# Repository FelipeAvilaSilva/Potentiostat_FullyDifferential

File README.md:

# Potentiostat_FullyDifferential
 Desenvolvimento de um Potenciostato Diferencial para detecção de metais pesados em corpos aquáticos

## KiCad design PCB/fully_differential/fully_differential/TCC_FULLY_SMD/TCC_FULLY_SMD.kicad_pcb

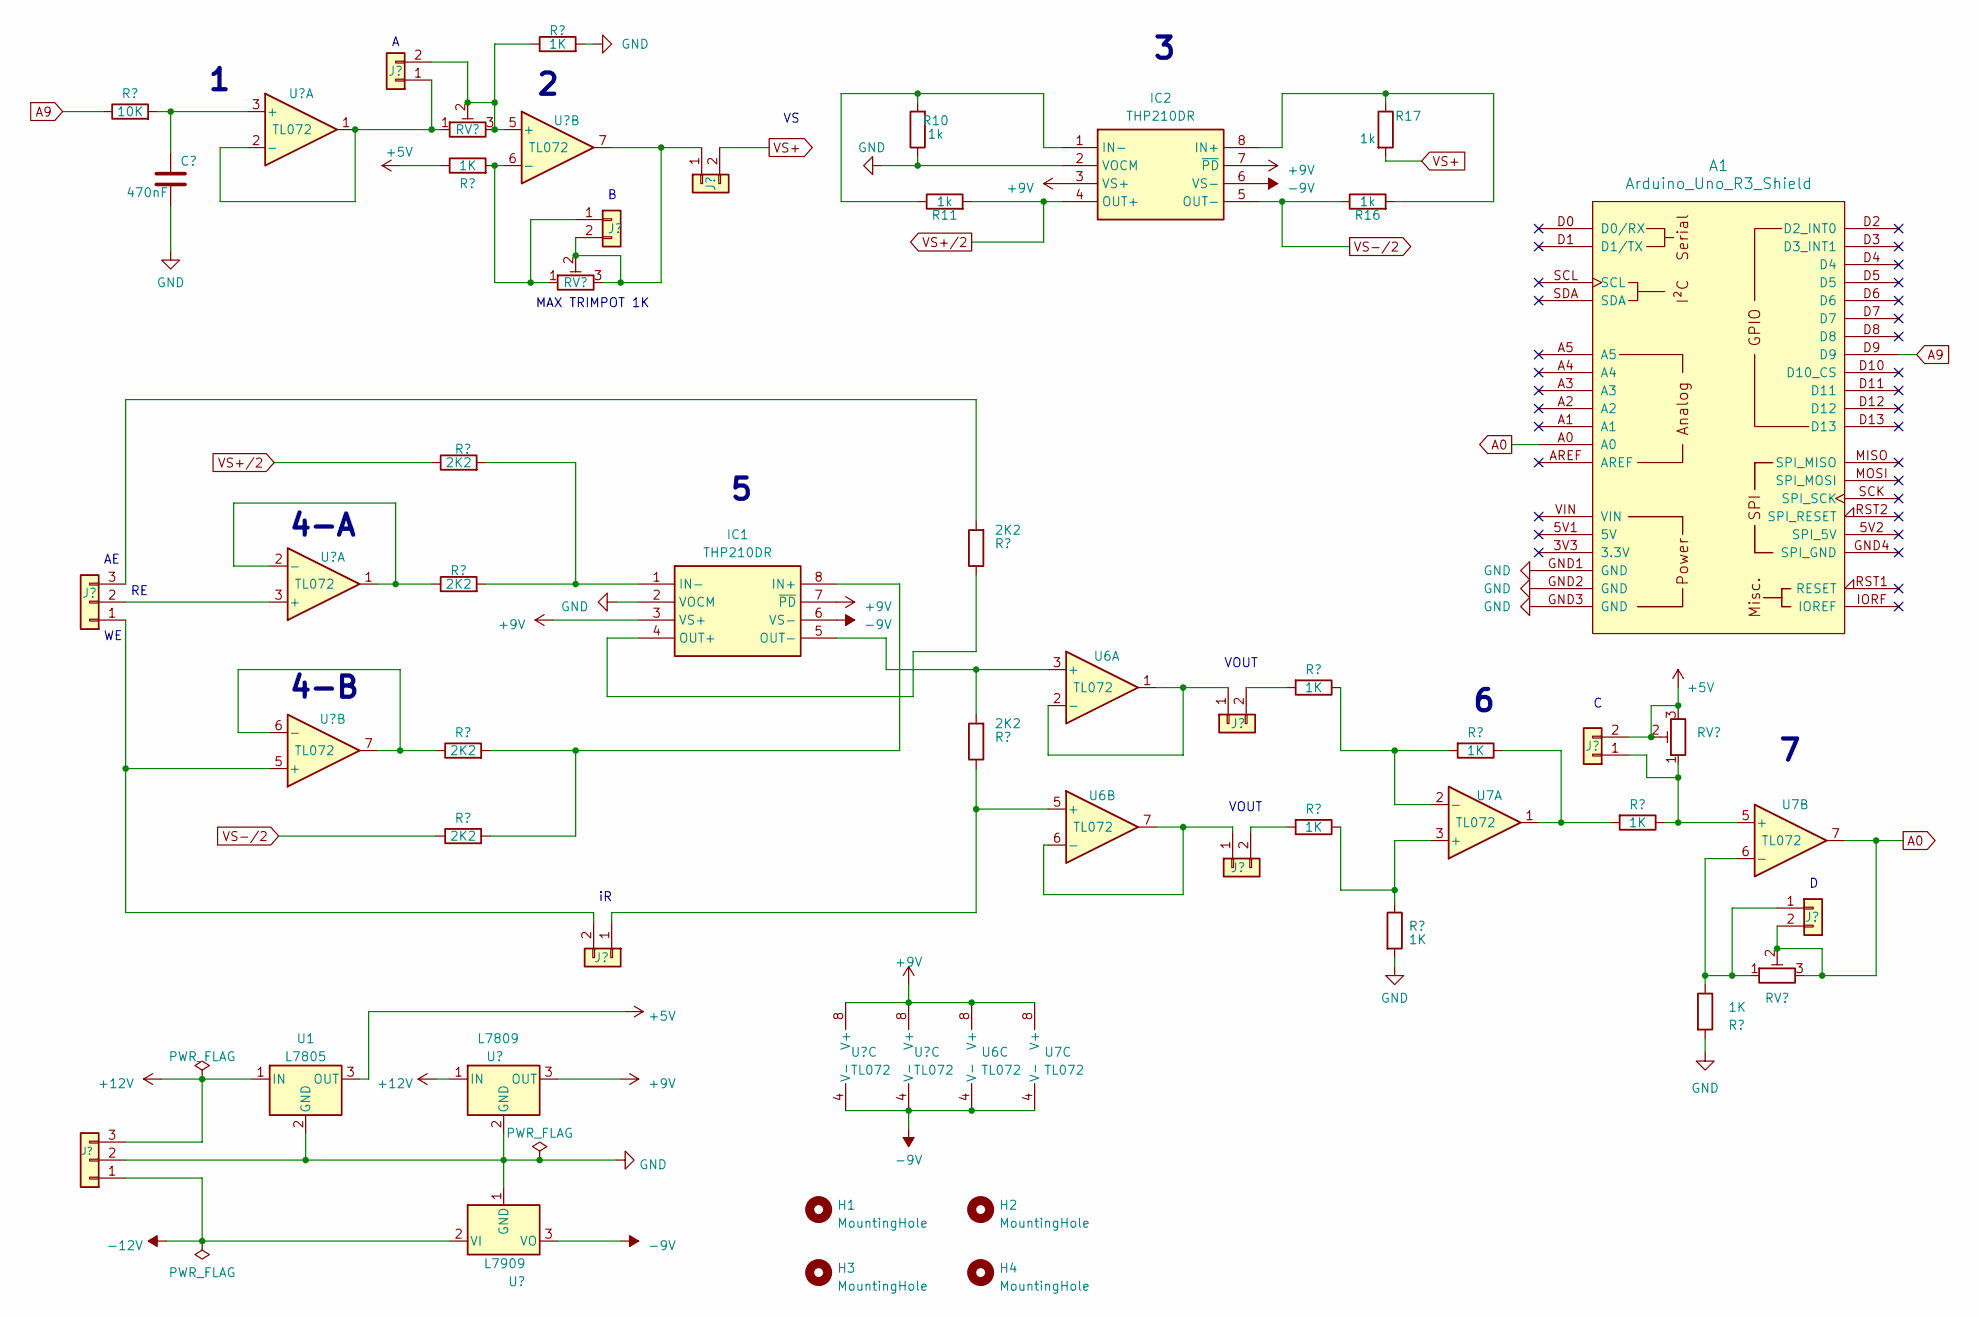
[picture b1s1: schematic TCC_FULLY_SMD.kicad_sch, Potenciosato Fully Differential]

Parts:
A1: Arduino_Uno_R3_Shield
C2: 470nF; C_Rect_L19.0mm_W6.0mm_P15.00mm_MKS4
H1, H2, H3, H4: MountingHole; MountingHole_3mm_Pad
IC1, IC2: THP210DR; SOIC127P600X175-8N; Mouser Part Number 595-THP210DR
J1: Conn_01x03; PinSocket_1x03_P2.54mm_Vertical
J2: Conn_01x03; Stocko_MKS_1653-6-0-303_1x3_P2.50mm_Vertical
J3, J4, J5, J6, J7, J8, J10, J11: Conn_01x02; PinHeader_1x02_P2.54mm_Vertical
R1: 10K; R_0805_2012Metric_Pad1.20x1.40mm_HandSolder
R2, R3, R4, R5, R8, R9: 2K2; R_0805_2012Metric_Pad1.20x1.40mm_HandSolder
R6, R7, R12, R13, R14, R15, R18, R19: 1K; R_0805_2012Metric_Pad1.20x1.40mm_HandSolder
R10, R11, R16, R17: 1k; R_0805_2012Metric_Pad1.20x1.40mm_HandSolder
RV1, RV2, RV3, RV4: R_Potentiometer_Trim; Potentiometer_Bourns_3296W_Vertical
U1: L7805; TO255P460X1020X2008-3P
U2, U3, U6, U7: TL072; DIP-8_W7.62mm_Socket_LongPads
U4: L7809; TO255P460X1020X2008-3P
U5: L7909; TO255P460X1020X2008-3P

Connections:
+5V: J10.2, R6.1, RV3.2, RV3.3, U1.3 (OUT)
+9V: IC1.3 (VS+), IC1.7 (~PD), IC2.3 (VS+), IC2.7 (~PD), U2.8 (V+), U3.8 (V+), U4.3 (OUT), U6.8 (V+), U7.8 (V+)
+12V: J2.3, U1.1 (IN), U4.1 (IN)
-9V: IC1.6 (VS-), IC2.6 (VS-), U2.4 (V-), U3.4 (V-), U5.3 (VO), U6.4 (V-), U7.4 (V-)
-12V: J2.1, U5.2 (VI)
A0: A1.A0, J11.2, RV4.2, RV4.3, U7.7
A9: A1.D9, R1.1
GND: A1.GND1 (GND), A1.GND2 (GND), A1.GND3 (GND), C2.2, IC1.2 (VOCM), IC2.2 (VOCM), J2.2, R7.2, R10.1, R14.2, R19.2, U1.2 (GND), U4.2 (GND), U5.1 (GND)
unnamed: IC1.8 (IN+), R4.2, R5.2
unnamed: IC1.1 (IN-), R2.2, R3.2
unnamed: IC1.4 (OUT+), R8.1
unnamed: IC1.5 (OUT-), R9.2, U6.3 (+)
unnamed: IC2.8 (IN+), R16.2, R17.1
unnamed: IC2.1 (IN-), R10.2, R11.1
unnamed: J1.1, J4.2, U2.5 (+)
unnamed: J1.2, U2.3 (+)
unnamed: J1.3, R8.2
unnamed: J3.1, RV1.1, U3.1, U3.2 (-)
unnamed: J3.2, R7.1, RV1.2, RV1.3, U3.5 (+)
unnamed: J4.1, R9.1, U6.5 (+)
unnamed: J5.1, R6.2, RV2.1, U3.6 (-)
unnamed: J5.2, J6.1, RV2.2, RV2.3, U3.7
unnamed: J7.1, U6.1, U6.2 (-)
unnamed: J7.2, R12.2
unnamed: J8.1, U6.6 (-), U6.7
unnamed: J8.2, R13.2
unnamed: J10.1, R18.1, RV3.1, U7.5 (+)
unnamed: J11.1, R19.1, RV4.1, U7.6 (-)
unnamed: R15.1, R18.2, U7.1
unnamed: R3.1, U2.1, U2.2 (-)
unnamed: R4.1, U2.6 (-), U2.7
unnamed: C2.1, R1.2, U3.3 (+)
unnamed: R13.1, R14.1, U7.3 (+)
unnamed: R12.1, R15.2, U7.2 (-)
VS+: J6.2, R17.2
VS+/2: IC2.4 (OUT+), R2.1, R11.2
VS-/2: IC2.5 (OUT-), R5.1, R16.1

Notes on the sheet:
VOUT
4-B
4-A
MAX TRIMPOT 1K

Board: 2 copper layers, 48 parts (0 on the bottom side), 37 nets, no tracks yet.

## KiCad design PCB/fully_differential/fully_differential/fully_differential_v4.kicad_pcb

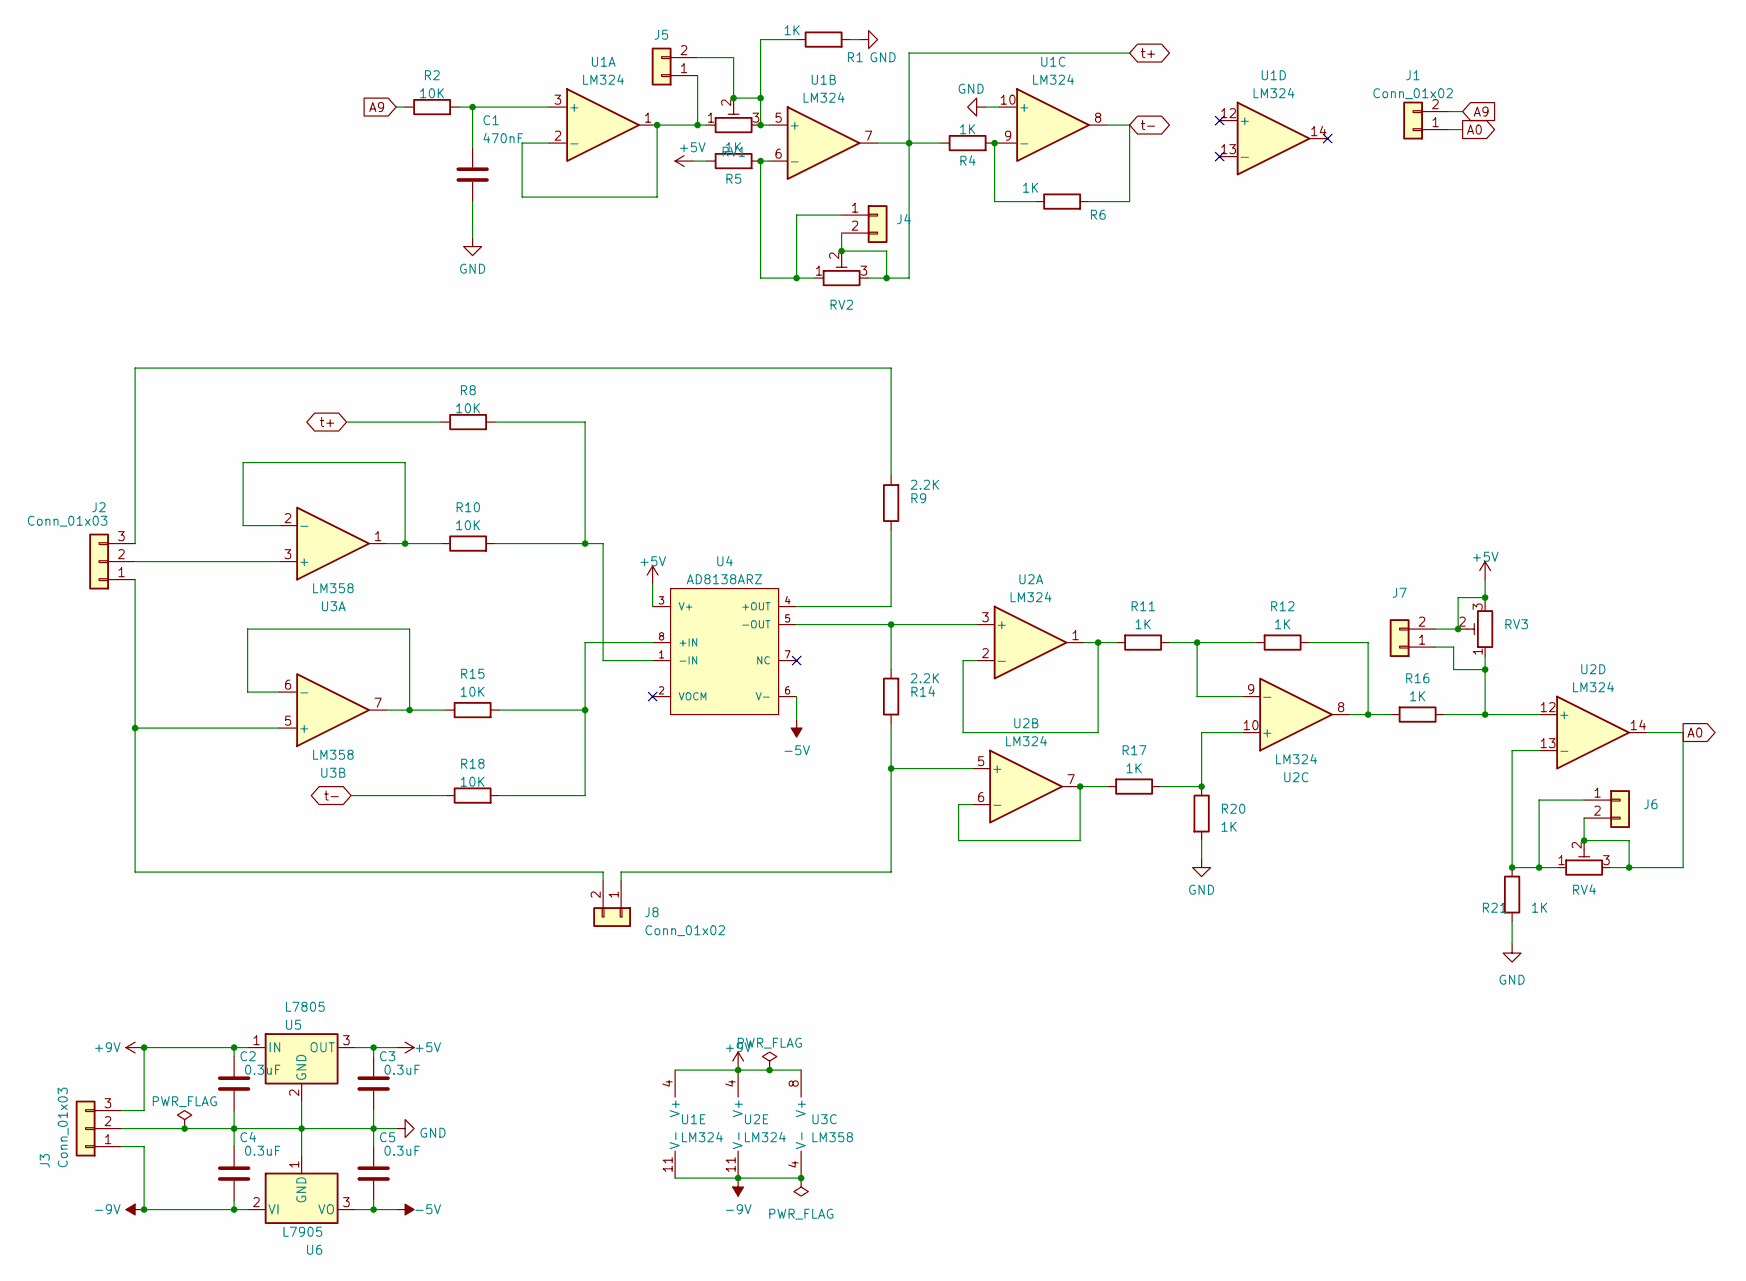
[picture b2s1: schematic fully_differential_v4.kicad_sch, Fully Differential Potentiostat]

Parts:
C1: 470nF; C_Rect_L19.0mm_W6.0mm_P15.00mm_MKS4
C2, C3, C4, C5: 0.3uF; CP_Radial_D5.0mm_P2.00mm
J1, J4, J5, J6, J7, J8: Conn_01x02; PinHeader_1x02_P2.54mm_Vertical
J2, J3: Conn_01x03; PinSocket_1x03_P2.54mm_Vertical
R1, R4, R5, R6, R11, R12, R16, R17, R20, R21: 1K; R_Axial_DIN0207_L6.3mm_D2.5mm_P10.16mm_Horizontal
R2, R8, R10, R15, R18: 10K; R_Axial_DIN0207_L6.3mm_D2.5mm_P10.16mm_Horizontal
R9, R14: 2.2K; R_Axial_DIN0207_L6.3mm_D2.5mm_P10.16mm_Horizontal
RV1, RV2, RV3, RV4: R_Potentiometer_Trim; Potentiometer_Bourns_3296W_Vertical
U1, U2: LM324; DIP-14_W7.62mm_Socket_LongPads
U3: LM358; DIP-8_W7.62mm_Socket_LongPads
U4: AD8138ARZ; ANALOG_DEVICES_INC_AD8138ARZ_0; mouser part number 584-AD8138ARZ; digikey description IC AMP DIFF LDIST LP 95MA 8SOIC
U5: L7805; TO255P1020X450X2000-3
U6: L7905; TO255P1020X450X2000-3

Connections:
+5V: C3.1, J7.2, R5.1, RV3.2, RV3.3, U4.3 (V+), U5.3 (OUT)
+9V: C2.1, J3.3, U1.4 (V+), U2.4 (V+), U3.8 (V+), U5.1 (IN)
-5V: C5.2, U4.6 (V-), U6.3 (VO)
-9V: C4.2, J3.1, U1.11 (V-), U2.11 (V-), U3.4 (V-), U6.2 (VI)
A0: J1.1, J6.2, RV4.2, RV4.3, U2.14
A9: J1.2, R2.1
GND: C1.2, C2.2, C3.2, C4.1, C5.1, J3.2, R1.2, R20.2, R21.2, U1.10 (+), U5.2 (GND), U6.1 (GND)
unnamed: J2.1, J8.2, U3.5 (+)
unnamed: J2.2, U3.3 (+)
unnamed: J2.3, R9.2
unnamed: J4.1, R5.2, RV2.1, U1.6 (-)
unnamed: J5.1, RV1.1, U1.1, U1.2 (-)
unnamed: J5.2, R1.1, RV1.2, RV1.3, U1.5 (+)
unnamed: J6.1, R21.1, RV4.1, U2.13 (-)
unnamed: J7.1, R16.1, RV3.1, U2.12 (+)
unnamed: J8.1, R14.1, U2.5 (+)
unnamed: R12.1, R16.2, U2.8
unnamed: C1.1, R2.2, U1.3 (+)
unnamed: R4.2, R6.1, U1.9 (-)
unnamed: R14.2, U2.3 (+), U4.5 (-OUT)
unnamed: R11.2, U2.1, U2.2 (-)
unnamed: R17.2, U2.6 (-), U2.7
unnamed: R17.1, R20.1, U2.10 (+)
unnamed: R11.1, R12.2, U2.9 (-)
unnamed: R10.1, U3.1, U3.2 (-)
unnamed: R15.1, U3.6 (-), U3.7
unnamed: R15.2, R18.2, U4.8 (+IN)
unnamed: R9.1, U4.4 (+OUT)
unnamed: R8.2, R10.2, U4.1 (-IN)
t+: J4.2, R4.1, R8.1, RV2.2, RV2.3, U1.7
t-: R6.2, R18.1, U1.8

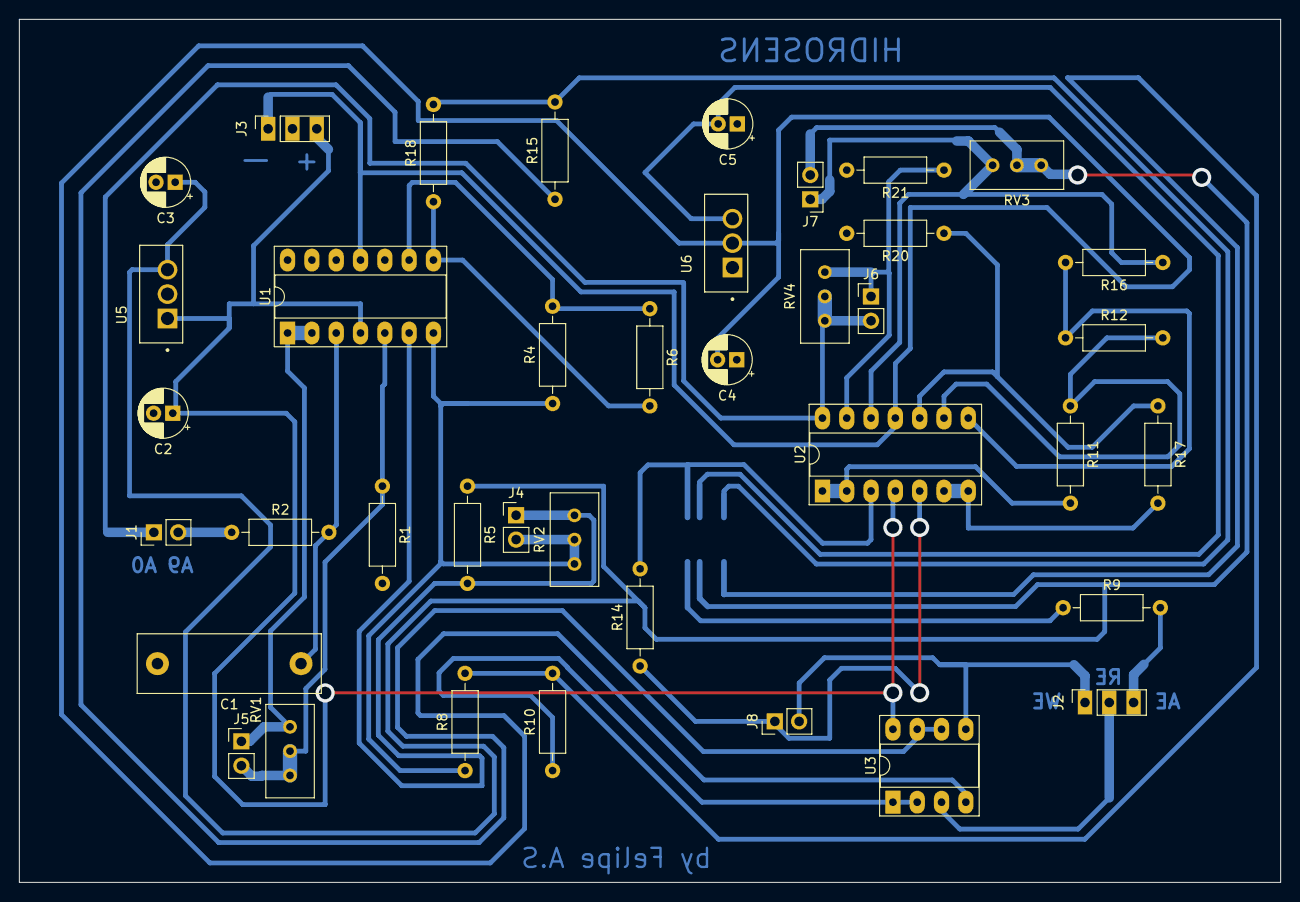
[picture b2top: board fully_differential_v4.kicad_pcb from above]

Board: 2 copper layers, 131.8 x 90.2 mm, 40 parts (1 on the bottom side), 31 nets.

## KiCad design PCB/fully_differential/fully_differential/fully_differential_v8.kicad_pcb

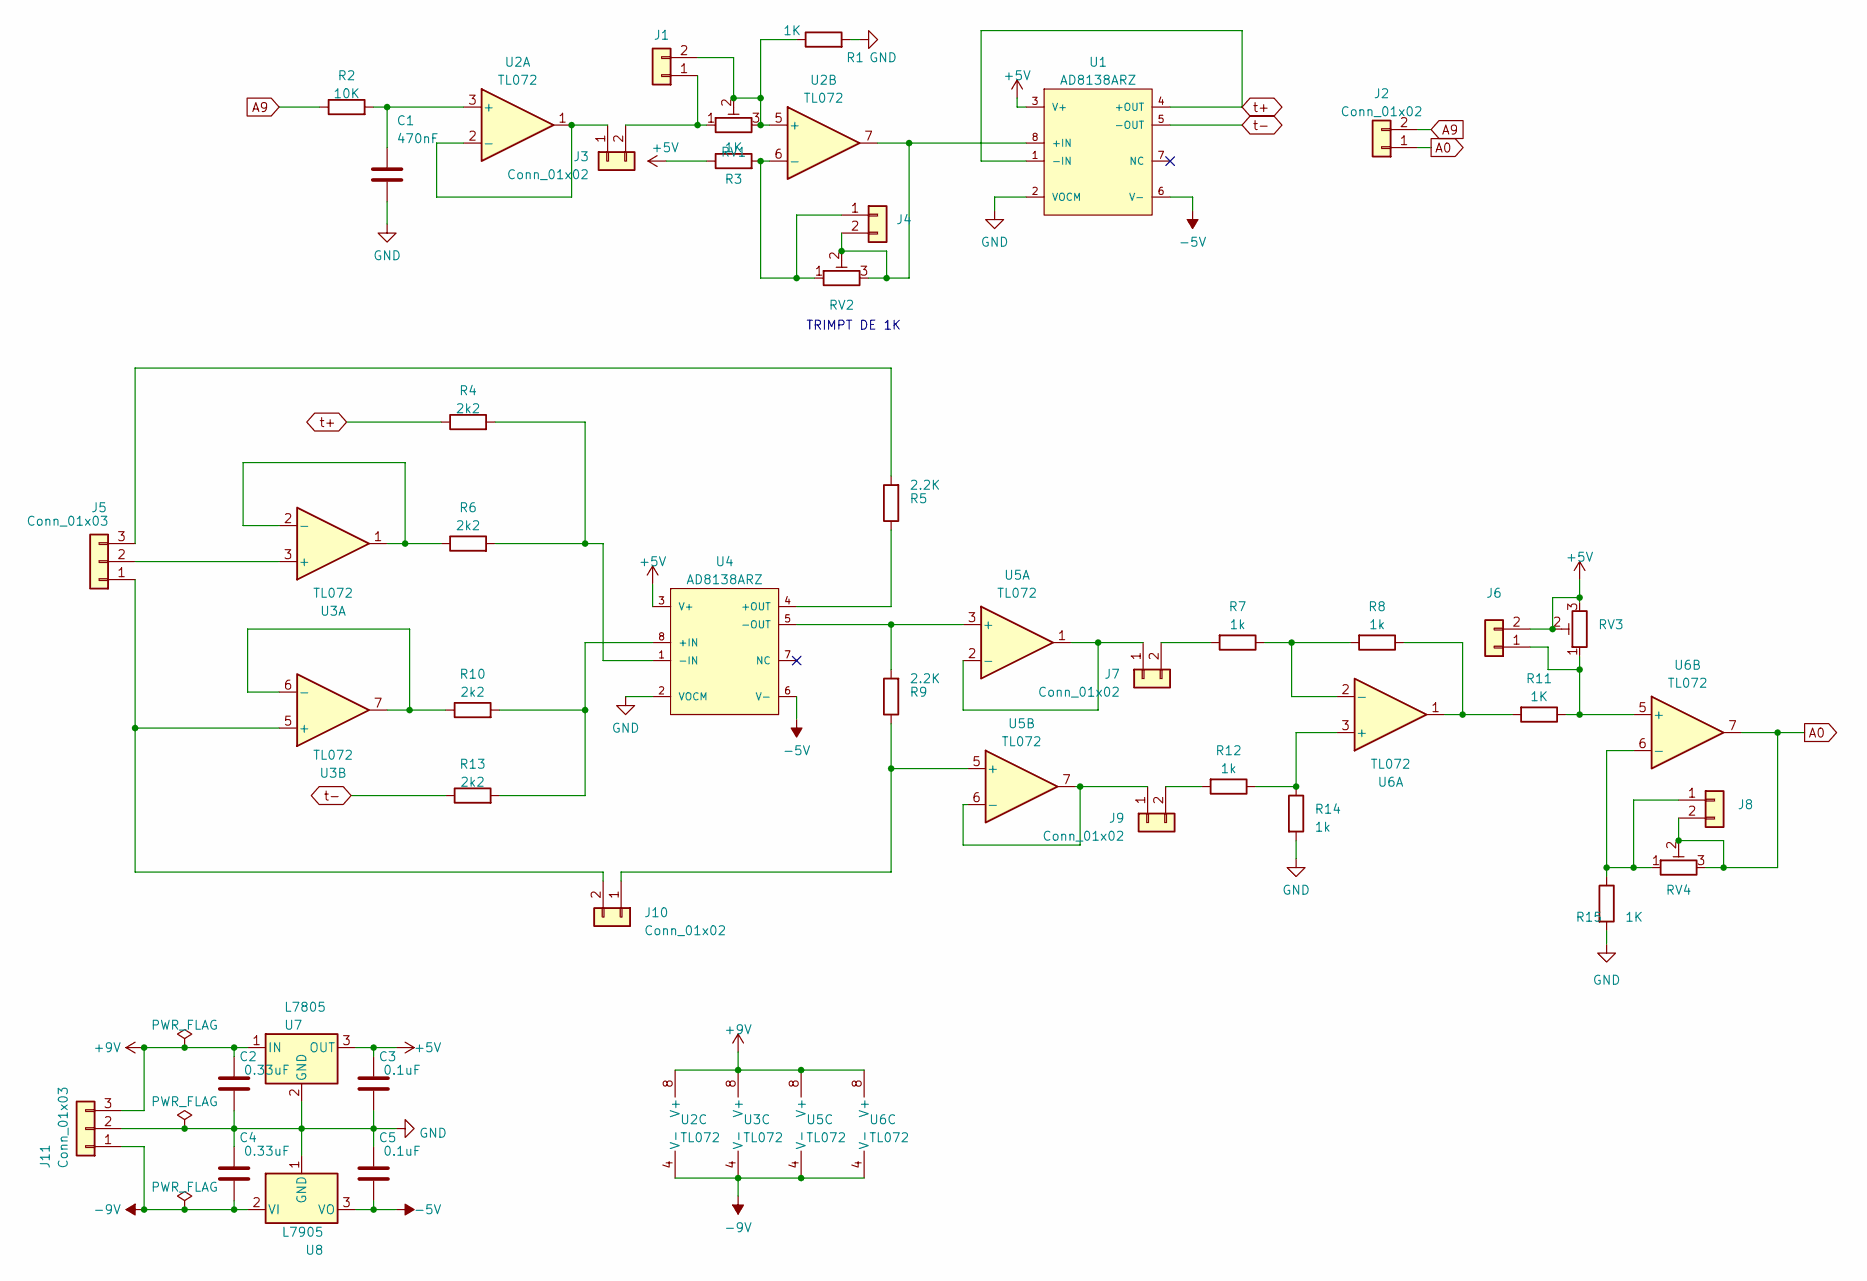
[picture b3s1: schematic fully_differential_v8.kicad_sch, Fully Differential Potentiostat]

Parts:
C1: 470nF; C_Rect_L19.0mm_W6.0mm_P15.00mm_MKS4
C2, C4: 0.33uF; CP_Radial_D5.0mm_P2.00mm
C3, C5: 0.1uF; CP_Radial_D5.0mm_P2.00mm
J1, J2, J3, J4, J6, J7, J8, J9, J10: Conn_01x02; PinHeader_1x02_P2.54mm_Vertical
J5, J11: Conn_01x03; PinSocket_1x03_P2.54mm_Vertical
R1, R3, R11, R15: 1K; R_Axial_DIN0207_L6.3mm_D2.5mm_P10.16mm_Horizontal
R2: 10K; R_Axial_DIN0207_L6.3mm_D2.5mm_P10.16mm_Horizontal
R4, R6, R10, R13: 2k2; R_Axial_DIN0207_L6.3mm_D2.5mm_P10.16mm_Horizontal
R5, R9: 2.2K; R_Axial_DIN0207_L6.3mm_D2.5mm_P10.16mm_Horizontal
R7, R8, R12, R14: 1k; R_Axial_DIN0207_L6.3mm_D2.5mm_P10.16mm_Horizontal
RV1, RV2, RV3, RV4: R_Potentiometer_Trim; Potentiometer_Bourns_3296W_Vertical
U1, U4: AD8138ARZ; ANALOG_DEVICES_INC_AD8138ARZ_0; mouser part number 584-AD8138ARZ; digikey description IC AMP DIFF LDIST LP 95MA 8SOIC
U2, U3, U5, U6: TL072; DIP-8_W7.62mm_Socket_LongPads
U7: L7805; TO255P1020X450X2000-3
U8: L7905; TO255P1020X450X2000-3

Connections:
+5V: C3.1, J6.2, R3.1, RV3.2, RV3.3, U1.3 (V+), U4.3 (V+), U7.3 (OUT)
+9V: C2.1, J11.3, U2.8 (V+), U3.8 (V+), U5.8 (V+), U6.8 (V+), U7.1 (IN)
-5V: C5.2, U1.6 (V-), U4.6 (V-), U8.3 (VO)
-9V: C4.2, J11.1, U2.4 (V-), U3.4 (V-), U5.4 (V-), U6.4 (V-), U8.2 (VI)
A0: J2.1, J8.2, RV4.2, RV4.3, U6.7
A9: J2.2, R2.1
GND: C1.2, C2.2, C3.2, C4.1, C5.1, J11.2, R1.2, R14.2, R15.2, U1.2 (VOCM), U4.2 (VOCM), U7.2 (GND), U8.1 (GND)
unnamed: J1.1, J3.2, RV1.1
unnamed: J1.2, R1.1, RV1.2, RV1.3, U2.5 (+)
unnamed: J3.1, U2.1, U2.2 (-)
unnamed: J4.1, R3.2, RV2.1, U2.6 (-)
unnamed: J4.2, RV2.2, RV2.3, U1.8 (+IN), U2.7
unnamed: J5.2, U3.3 (+)
unnamed: J5.3, R5.2
unnamed: J6.1, R11.1, RV3.1, U6.5 (+)
unnamed: J7.1, U5.1, U5.2 (-)
unnamed: J7.2, R7.2
unnamed: J8.1, R15.1, RV4.1, U6.6 (-)
unnamed: J9.1, U5.6 (-), U5.7
unnamed: J9.2, R12.2
unnamed: J10.1, R9.1, U5.5 (+)
unnamed: J5.1, J10.2, U3.5 (+)
unnamed: R8.1, R11.2, U6.1
unnamed: C1.1, R2.2, U2.3 (+)
unnamed: R6.1, U3.1, U3.2 (-)
unnamed: R10.1, U3.6 (-), U3.7
unnamed: R10.2, R13.2, U4.8 (+IN)
unnamed: R5.1, U4.4 (+OUT)
unnamed: R4.2, R6.2, U4.1 (-IN)
unnamed: R9.2, U4.5 (-OUT), U5.3 (+)
unnamed: R12.1, R14.1, U6.3 (+)
unnamed: R7.1, R8.2, U6.2 (-)
t+: R4.1, U1.1 (-IN), U1.4 (+OUT)
t-: R13.1, U1.5 (-OUT)

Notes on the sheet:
TRIMPT DE 1K

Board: 2 copper layers, 43 parts (2 on the bottom side), 34 nets, no tracks yet.

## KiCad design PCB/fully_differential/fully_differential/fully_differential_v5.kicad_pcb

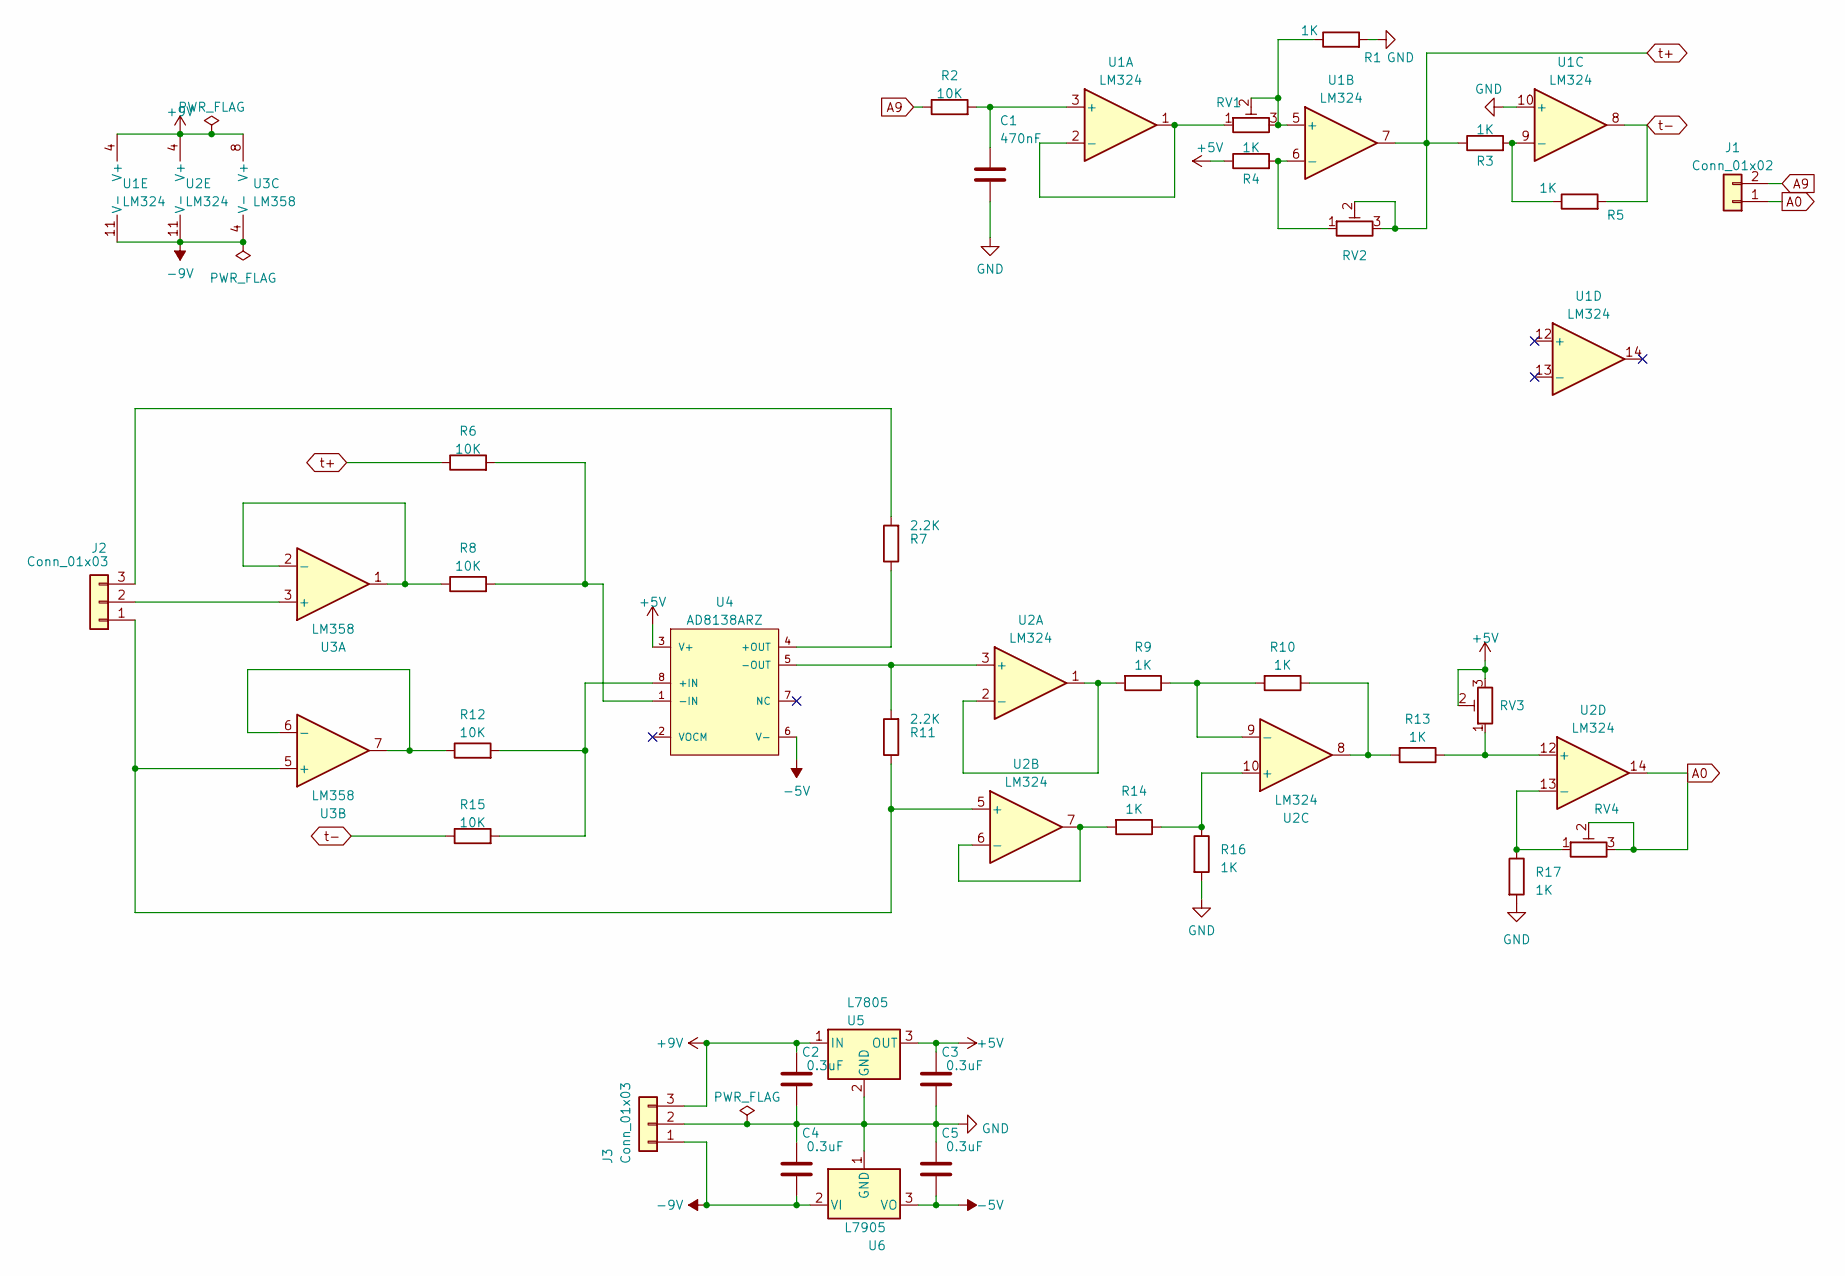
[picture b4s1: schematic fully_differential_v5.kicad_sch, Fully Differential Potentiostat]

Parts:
C1: 470nF; C_Rect_L19.0mm_W6.0mm_P15.00mm_MKS4
C2, C3, C4, C5: 0.3uF; CP_Radial_D5.0mm_P2.00mm
J1: Conn_01x02; PinSocket_1x02_P2.54mm_Vertical
J2, J3: Conn_01x03; PinSocket_1x03_P2.54mm_Vertical
R1, R3, R4, R5, R9, R10, R13, R14, R16, R17: 1K; R_Axial_DIN0207_L6.3mm_D2.5mm_P10.16mm_Horizontal
R2, R6, R8, R12, R15: 10K; R_Axial_DIN0207_L6.3mm_D2.5mm_P10.16mm_Horizontal
R7, R11: 2.2K; R_Axial_DIN0207_L6.3mm_D2.5mm_P10.16mm_Horizontal
RV1, RV2, RV3, RV4: R_Potentiometer_Trim; Potentiometer_Bourns_3296W_Vertical
U1, U2: LM324; DIP-14_W7.62mm_Socket_LongPads
U3: LM358; DIP-8_W7.62mm_Socket_LongPads
U4: AD8138ARZ; ANALOG_DEVICES_INC_AD8138ARZ_0; mouser part number 584-AD8138ARZ; digikey description IC AMP DIFF LDIST LP 95MA 8SOIC
U5: L7805; TO255P1020X450X2000-3
U6: L7905; TO255P1020X450X2000-3

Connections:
+5V: C3.1, R4.1, RV3.2, RV3.3, U4.3 (V+), U5.3 (OUT)
+9V: C2.1, J3.3, U1.4 (V+), U2.4 (V+), U3.8 (V+), U5.1 (IN)
-5V: C5.2, U4.6 (V-), U6.3 (VO)
-9V: C4.2, J3.1, U1.11 (V-), U2.11 (V-), U3.4 (V-), U6.2 (VI)
A0: J1.1, RV4.2, RV4.3, U2.14
A9: J1.2, R2.1
GND: C1.2, C2.2, C3.2, C4.1, C5.1, J3.2, R1.2, R16.2, R17.2, U1.10 (+), U5.2 (GND), U6.1 (GND)
unnamed: J2.1, R11.1, U2.5 (+), U3.5 (+)
unnamed: J2.2, U3.3 (+)
unnamed: J2.3, R7.2
unnamed: R10.1, R13.2, U2.8
unnamed: C1.1, R2.2, U1.3 (+)
unnamed: RV1.1, U1.1, U1.2 (-)
unnamed: R1.1, RV1.2, RV1.3, U1.5 (+)
unnamed: R4.2, RV2.1, U1.6 (-)
unnamed: R3.2, R5.1, U1.9 (-)
unnamed: R11.2, U2.3 (+), U4.5 (-OUT)
unnamed: R9.2, U2.1, U2.2 (-)
unnamed: R14.2, U2.6 (-), U2.7
unnamed: R14.1, R16.1, U2.10 (+)
unnamed: R9.1, R10.2, U2.9 (-)
unnamed: R13.1, RV3.1, U2.12 (+)
unnamed: R17.1, RV4.1, U2.13 (-)
unnamed: R8.1, U3.1, U3.2 (-)
unnamed: R12.1, U3.6 (-), U3.7
unnamed: R12.2, R15.2, U4.8 (+IN)
unnamed: R7.1, U4.4 (+OUT)
unnamed: R6.2, R8.2, U4.1 (-IN)
t+: R3.1, R6.1, RV2.2, RV2.3, U1.7
t-: R5.2, R15.1, U1.8

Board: 2 copper layers, 35 parts (0 on the bottom side), 30 nets, no tracks yet.

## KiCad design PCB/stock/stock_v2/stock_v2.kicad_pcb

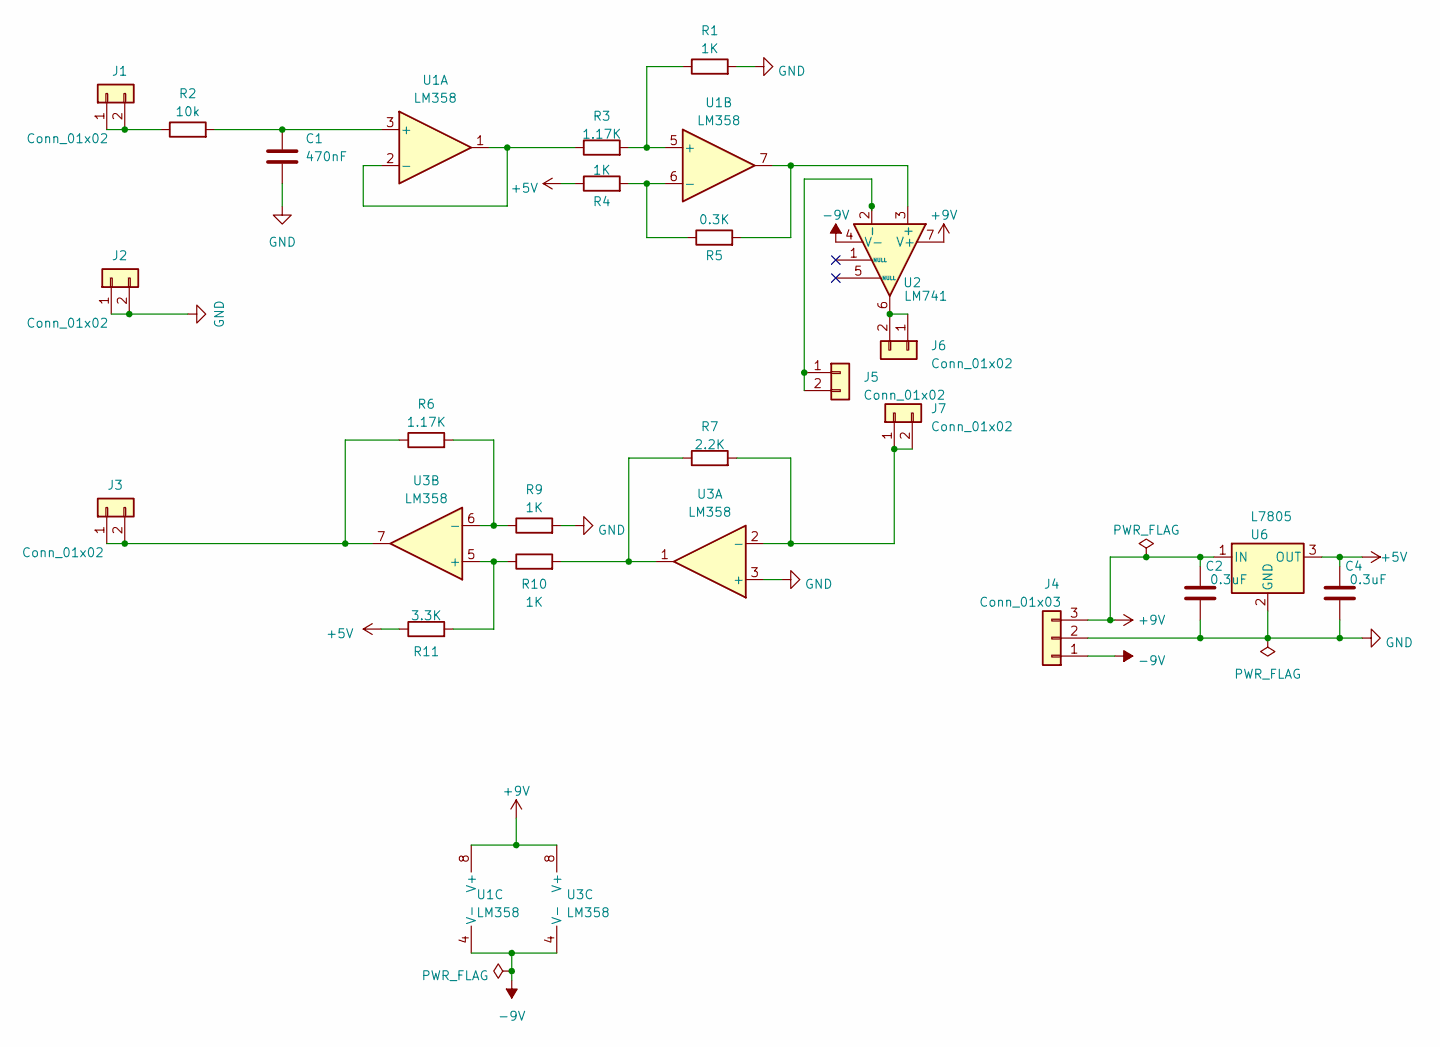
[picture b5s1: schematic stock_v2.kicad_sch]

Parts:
C1: 470nF; C_Rect_L19.0mm_W6.0mm_P15.00mm_MKS4
C2, C4: 0.3uF; CP_Radial_D5.0mm_P2.00mm
J1, J2, J3, J5, J6, J7: Conn_01x02; PinSocket_1x02_P2.54mm_Vertical
J4: Conn_01x03; PinSocket_1x03_P2.54mm_Vertical
R1, R4, R9, R10: 1K; R_Axial_DIN0207_L6.3mm_D2.5mm_P10.16mm_Horizontal
R2: 10k; R_Axial_DIN0207_L6.3mm_D2.5mm_P10.16mm_Horizontal
R3, R6: 1.17K; R_Axial_DIN0207_L6.3mm_D2.5mm_P10.16mm_Horizontal
R5: 0.3K; R_Axial_DIN0207_L6.3mm_D2.5mm_P10.16mm_Horizontal
R7: 2.2K; R_Axial_DIN0207_L6.3mm_D2.5mm_P10.16mm_Horizontal
R11: 3.3K; R_Axial_DIN0207_L6.3mm_D2.5mm_P10.16mm_Horizontal
U1, U3: LM358; DIP-8_W7.62mm_LongPads
U2: LM741; DIP-8_W7.62mm_LongPads
U6: L7805; TO255P1020X450X2000-3

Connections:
+5V: R4.1, R11.1; also elsewhere on the board
+9V: C2.1, J4.3, U1.8 (V+), U2.7 (V+), U3.8 (V+); also elsewhere on the board
-9V: J4.1, U1.4 (V-), U2.4 (V-), U3.4 (V-)
GND: C1.2, C2.2, J2.1, J2.2, J4.2, R1.2, R9.2, U3.3 (+); also elsewhere on the board
unnamed: J1.1, J1.2, R2.1
unnamed: J3.1, J3.2, R6.1, U3.7
unnamed: J5.1, J5.2, U2.2 (-)
unnamed: J6.1, J6.2, U2.6
unnamed: J7.1, J7.2, R7.2, U3.2 (-)
unnamed: R7.1, R10.2, U3.1
unnamed: C1.1, R2.2, U1.3 (+)
unnamed: R3.1, U1.1, U1.2 (-)
unnamed: R1.1, R3.2, U1.5 (+)
unnamed: R4.2, R5.1, U1.6 (-)
unnamed: R5.2, U1.7, U2.3 (+)
unnamed: R10.1, R11.2, U3.5 (+)
unnamed: R6.2, R9.1, U3.6 (-)

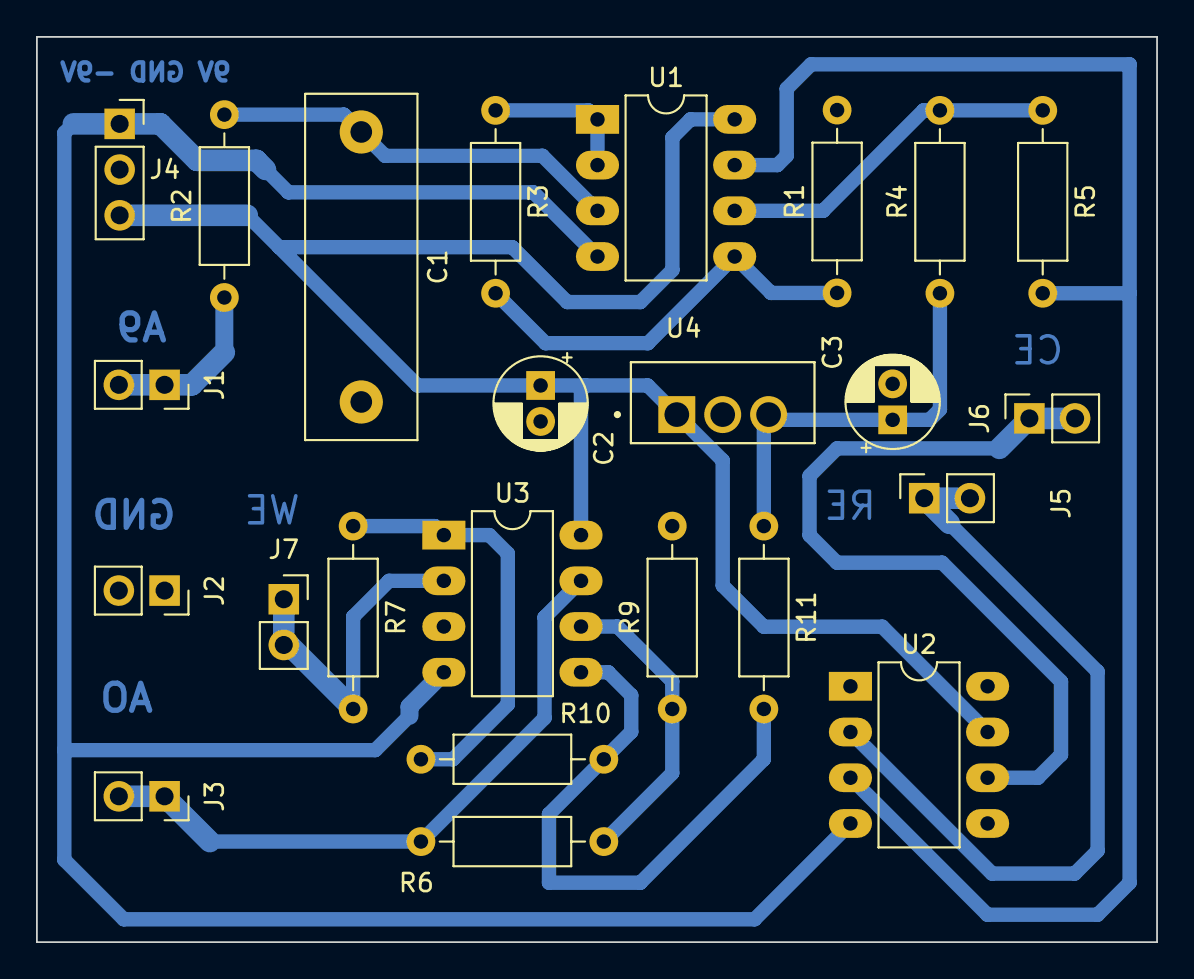
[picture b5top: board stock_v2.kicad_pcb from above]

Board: 2 copper layers, 62.2 x 50.3 mm, 24 parts (0 on the bottom side), 17 nets.

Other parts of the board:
C3: 0.3uF; CP_Radial_D5.0mm_P2.00mm
U4: L7805; TO255P1020X450X2000-3

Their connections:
+5V: C3.1, U4.3 (OUT); also elsewhere on the board
+9V: U4.1 (IN); also elsewhere on the board
GND: C3.2, U4.2 (GND); also elsewhere on the board

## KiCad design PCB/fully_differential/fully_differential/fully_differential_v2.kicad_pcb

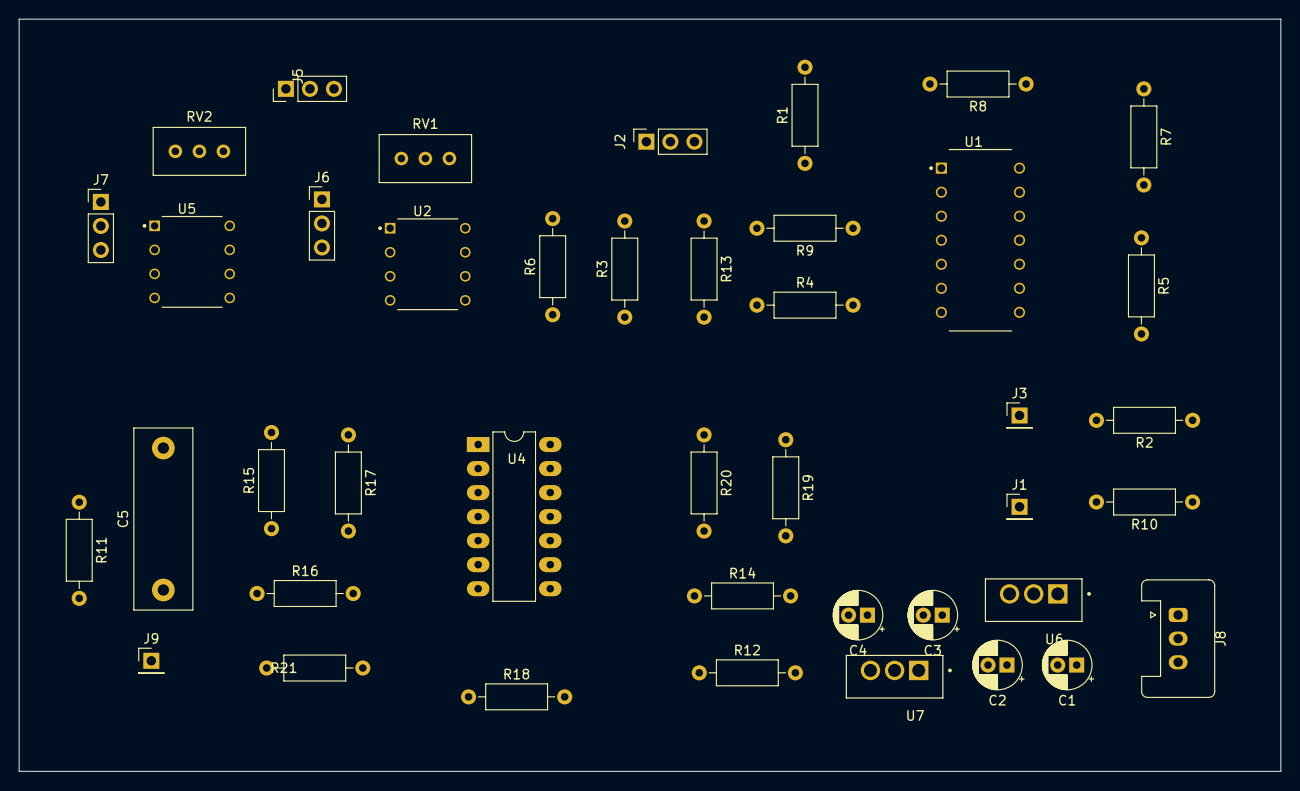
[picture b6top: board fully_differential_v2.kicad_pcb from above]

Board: 2 copper layers, 133.3 x 79.5 mm, 43 parts (1 on the bottom side), 37 nets, no tracks yet.

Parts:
C1, C2, C3, C4: 0.3uF; CP_Radial_D5.0mm_P2.00mm
C5: 470nF; C_Rect_L19.0mm_W6.0mm_P15.00mm_MKS4
J1: PIN_A0; PinHeader_1x01_P2.54mm_Vertical
J2: Conn_01x03; PinSocket_1x03_P2.54mm_Vertical
J3: Conn_01x01; PinHeader_1x01_P2.54mm_Vertical
J5, J6, J7: Conn_01x03; PinHeader_1x03_P2.54mm_Vertical
J8: Conn_01x03; Stocko_MKS_1653-6-0-303_1x3_P2.50mm_Vertical
J9: PIN_09; PinHeader_1x01_P2.54mm_Vertical
R1, R2, R5, R8, R9, R10, R15, R18, R19, R20: 1K; R_Axial_DIN0207_L6.3mm_D2.5mm_P10.16mm_Horizontal
R3, R11, R12, R14, R16: 10K; R_Axial_DIN0207_L6.3mm_D2.5mm_P10.16mm_Horizontal
R4: 3.3K; R_Axial_DIN0207_L6.3mm_D2.5mm_P10.16mm_Horizontal
R6, R13: 2.2K; R_Axial_DIN0207_L6.3mm_D2.5mm_P10.16mm_Horizontal
R7: 1.17K; R_Axial_DIN0207_L6.3mm_D2.5mm_P10.16mm_Horizontal
R17: 2.83K; R_Axial_DIN0207_L6.3mm_D2.5mm_P10.16mm_Horizontal
R21: 150; R_Axial_DIN0207_L6.3mm_D2.5mm_P10.16mm_Horizontal
RV1, RV2: R_Potentiometer_Trim; Potentiometer_Bourns_3296W_Vertical
U1: LM324; DIP825W47P254L1917H533Q14
U2, U5: LM741; DIP794W45P254L959H508Q8
U3: AD8138ARZ; ANALOG_DEVICES_INC_AD8138ARZ_0
U4: LM324; DIP-14_W7.62mm_LongPads
U6: L7805; TO255P1020X450X2000-3
U7: L7905; TO255P1020X450X2000-3

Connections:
+5V: C2.1, R4.1, R19.1, U3.3 (V+), U6.3 (OUT)
+9V: C1.1, J8.3, U2.7 (V+), U4.4 (V+), U5.7 (V+), U6.1 (IN)
-5V: C4.2, U3.6 (V-), U7.3 (VO)
-9V: C3.2, J5.1, J8.1, U2.4 (V-), U4.11 (V-), U5.4 (V-), U7.2 (VI)
GND: C1.2, C2.2, C3.1, C4.1, C5.2, J3.1, J8.2, R9.2, R10.2, R15.2, U4.10 (+), U6.2 (GND), U7.1 (GND)
unnamed: J1.1, R7.1, U1.14
unnamed: J2.1, R13.1, U5.3 (+)
unnamed: J2.2, U2.3 (+)
unnamed: J2.3, R6.2, U1.3 (+)
unnamed: J5.2, RV1.2, RV2.2
unnamed: J6.2, RV1.3
unnamed: J7.2, RV2.3
unnamed: J9.1, R16.1
unnamed: R2.1, R5.2, U1.8
unnamed: R1.2, U1.1, U1.2 (-)
unnamed: R6.1, U1.5 (+), U3.4 (+OUT)
unnamed: R8.2, U1.6 (-), U1.7
unnamed: R8.1, R10.1, U1.10 (+)
unnamed: R1.1, R2.2, U1.9 (-)
unnamed: R4.2, R5.1, U1.12 (+)
unnamed: R7.2, R9.1, U1.13 (-)
unnamed: R11.1, U2.2 (-), U2.6
unnamed: R12.2, R14.2, U3.8 (+IN)
unnamed: R3.2, R11.2, U3.1 (-IN)
unnamed: R13.2, U3.5 (-OUT)
unnamed: C5.1, R16.2, U4.3 (+)
unnamed: R17.1, U4.1, U4.2 (-)
unnamed: R15.1, R17.2, U4.5 (+)
unnamed: R19.2, R21.1, U4.6 (-)
unnamed: R18.2, R20.1, U4.9 (-)
unnamed: R12.1, U5.2 (-), U5.6
op2_1: J6.1, U2.1 (NULL)
op2_2: RV1.1, U2.5 (NULL)
op3_1: J7.1, U5.1 (NULL)
op3_2: RV2.1, U5.5 (NULL)
t+: R3.1, R18.1, R21.2, U4.7
t-: R14.1, R20.2, U4.8
